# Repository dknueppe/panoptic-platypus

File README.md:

# Panoptic Platypus

This here is a new repository for an OSH/OSS data logger it will feature the
Lattice ecp5 for communication data processing. At this point there is no further
information.

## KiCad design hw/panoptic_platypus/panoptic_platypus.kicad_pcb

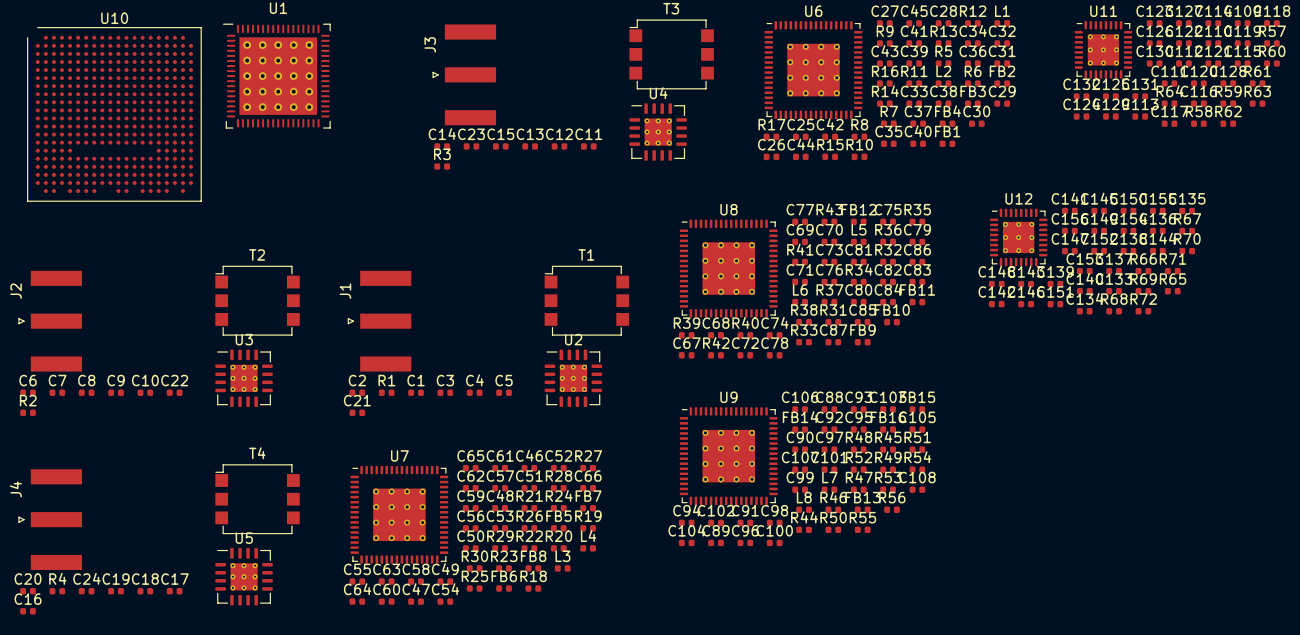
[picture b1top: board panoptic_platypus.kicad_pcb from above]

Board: 2 copper layers, 272 parts (0 on the bottom side), 218 nets, no tracks yet.

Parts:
C1, C6, C11, C16: 0.3p; C_0402_1005Metric
C2, C3, C7, C8, C12, C13, C17, C18, C25, C26, C27, C28, C31, C32, C33, C34, C38, C40, C41, C42, C43, C46, C47, C48, C49, C52, C53, C54, C55, C59, C61, C62, C63, C64, C67, C68, C69, C70, C73, C74, C75, C76, C80, C82, C83, C84, C85, C88, C89, C90, C91, C94, C95, C96, C97, C101, C103, C104, C105, C106, C115, C118, C122, C124, C127, C129, C131, C139, C142, C146, C148, C151, C153, C155: 0.1u; C_0402_1005Metric
C4, C9, C14, C19: 0.05p; C_0402_1005Metric
C5, C10, C15, C20, C29, C30, C35, C36, C50, C51, C56, C57, C71, C72, C77, C78, C92, C93, C98, C99: 10n; C_0402_1005Metric
C21, C22, C23, C24, C37, C39, C58, C60, C79, C81, C100, C102, C117, C119, C126, C141, C143, C150: 1u; C_0402_1005Metric
C44, C45, C65, C66, C86, C87, C107, C108: 5p; C_0402_1005Metric
C109, C110, C111, C112, C116, C121, C125, C128, C130, C132, C133, C134, C135, C136, C140, C145, C149, C152, C154, C156: 100p; C_0402_1005Metric
C113, C114, C137, C138: 0.01u; C_0402_1005Metric
C120, C144: 820p; C_0402_1005Metric
C123, C147: 0.012u; C_0402_1005Metric
FB1, FB5, FB9, FB13: 10 @ 100MHz; C_0402_1005Metric
FB2, FB3, FB4, FB6, FB7, FB8, FB10, FB11, FB12, FB14, FB15, FB16: 10 @ 100 MHz; C_0402_1005Metric
J1, J2, J3, J4: Conn_Coaxial; SMA_Amphenol_132289_EdgeMount
L1, L2, L3, L4, L5, L6, L7, L8: 100n; L_0402_1005Metric
R1, R2, R3, R4: 4.75k; R_0402_1005Metric
R5, R6, R7, R18, R19, R20, R31, R32, R33, R44, R45, R46: 10k; R_0402_1005Metric
R8, R10, R11, R13, R21, R23, R24, R26, R34, R36, R37, R39, R47, R49, R50, R52: 33; R_0402_1005Metric
R9, R12, R22, R25, R35, R38, R48, R51: 49.9; R_0402_1005Metric
R14, R15, R16, R17, R27, R28, R29, R30, R40, R41, R42, R43, R53, R54, R55, R56: 66; R_0402_1005Metric
R57, R58, R59, R60, R65, R66, R67, R68: 50; R_0402_1005Metric
R61, R69: 90.9; R_0402_1005Metric
R62, R70: 30.1; R_0402_1005Metric
R63, R71: 240; R_0402_1005Metric
R64, R72: 5.1k; R_0402_1005Metric
T1, T2, T3, T4: MABA-011082; Pulse_P0926NL
U1: MAX2851; TQFN-68_EP_10x10_Pitch0.5mm_EP7.7mmx7.7mm_ThermalVias
U2, U3, U4, U5: LTC5510; QFN-16-1EP_5x5mm_P0.8mm_EP2.7x2.7mm_ThermalVias
U6, U7, U8, U9: AD9268; LFCSP-64-1EP_9x9mm_P0.5mm_EP5.21x5.21mm_ThermalVias
U10: ECP5_5G_25_CABGA381; Lattice_caBGA-381_17.0x17.0mm_Layout20x20_P0.8mm_Ball0.4mm_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
U11, U12: MAX2871; TQFN-32-1EP_5x5mm_P0.5mm_EP3.1x3.1mm_ThermalVias

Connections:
+1V8: C25.1, C26.1, C27.1, C28.1, C29.1, C30.1, C31.1, C32.1, C33.1, C34.1, C35.1, C36.1, C46.1, C47.1, C48.1, C49.1, C50.1, C51.1, C52.1, C53.1, C54.1, C55.1, C56.1, C57.1, C67.1, C68.1, C69.1, C70.1, C71.1, C72.1, C73.1, C74.1, C75.1, C76.1, C77.1, C78.1, C88.1, C89.1, C90.1, C91.1, C92.1, C93.1, C94.1, C95.1, C96.1, C97.1, C98.1, C99.1, R6.1, R7.1, R19.1, R20.1, R32.1, R33.1, R45.1, R46.1, U6.10, U6.19, U6.28, U6.37, U6.49, U6.50, U6.53, U6.54, U6.59, U6.60, U6.63, U6.64, U7.10, U7.19, U7.28, U7.37, U7.49, U7.50, U7.53, U7.54, U7.59, U7.60, U7.63, U7.64, U8.10, U8.19, U8.28, U8.37, U8.49, U8.50, U8.53, U8.54, U8.59, U8.60, U8.63, U8.64, U9.10, U9.19, U9.28, U9.37, U9.49, U9.50, U9.53, U9.54, U9.59, U9.60, U9.63, U9.64
+5V: C5.1, C10.1, C15.1, C20.1, C21.1, C22.1, C23.1, C24.1, U2.6, U2.7, U3.6, U3.7, U4.6, U4.7, U5.6, U5.7
/ADC Path2/CSB: R7.2, U6.46
/ADC Path2/OEB: R6.2, U6.47
/ADC Path 1/CSB: R33.2, U8.46
/ADC Path 1/OEB: R32.2, U8.47
/ADC Path 3/CSB: R20.2, U7.46
/ADC Path 3/OEB: R19.2, U7.47
/ADC Path 4/CSB: R46.2, U9.46
/ADC Path 4/OEB: R45.2, U9.47
/I_OUT_A0: U8.25, U10.B20
/I_OUT_A1: U8.26, U10.B19
/I_OUT_A2: U8.27, U10.A19
/I_OUT_A3: U8.29, U10.A18
/I_OUT_A4: U8.30, U10.B18
/I_OUT_A5: U8.31, U10.C17
/I_OUT_A6: U8.32, U10.A17
/I_OUT_A7: U8.33, U10.B17
/I_OUT_A8: U8.34, U10.D16
/I_OUT_A9: U8.35, U10.B16
/I_OUT_A10: U8.36, U10.C16
/I_OUT_A11: U8.38, U10.A16
/I_OUT_A12: U8.39, U10.E15
/I_OUT_A13: U8.40, U10.C15
/I_OUT_A14: U8.41, U10.D15
/I_OUT_A15: U8.42, U10.B15
/I_OUT_B0: U6.25, U10.T17
/I_OUT_B1: U6.26, U10.U16
/I_OUT_B2: U6.27, U10.U17
/I_OUT_B3: U6.29, U10.U18
/I_OUT_B4: U6.30, U10.T18
/I_OUT_B5: U6.31, U10.R18
/I_OUT_B6: U6.32, U10.U19
/I_OUT_B7: U6.33, U10.T19
/I_OUT_B8: U6.34, U10.U20
/I_OUT_B9: U6.35, U10.R20
/I_OUT_B10: U6.36, U10.T20
/I_OUT_B11: U6.38, U10.P20
/I_OUT_B12: U6.39, U10.P18
/I_OUT_B13: U6.40, U10.N20
/I_OUT_B14: U6.41, U10.P19
/I_OUT_B15: U6.42, U10.N19
/I_OUT_C0: U7.25, U10.G2
/I_OUT_C1: U7.26, U10.H2
/I_OUT_C2: U7.27, U10.F1
/I_OUT_C3: U7.29, U10.G1
/I_OUT_C4: U7.30, U10.J4
/I_OUT_C5: U7.31, U10.J3
/I_OUT_C6: U7.32, U10.J5
/I_OUT_C7: U7.33, U10.K3
/I_OUT_C8: U7.34, U10.K2
/I_OUT_C9: U7.35, U10.H1
/I_OUT_C10: U7.36, U10.J1
/I_OUT_C11: U7.38, U10.K1
/I_OUT_C12: U7.39, U10.K4
/I_OUT_C13: U7.40, U10.L4
/I_OUT_C14: U7.41, U10.K5
/I_OUT_C15: U7.42, U10.L5
/I_OUT_D0: U9.25, U10.K20
/I_OUT_D1: U9.26, U10.K19
/I_OUT_D2: U9.27, U10.J20
/I_OUT_D3: U9.29, U10.J19
/I_OUT_D4: U9.30, U10.K18
/I_OUT_D5: U9.31, U10.H20
/I_OUT_D6: U9.32, U10.J18
/I_OUT_D7: U9.33, U10.G19
/I_OUT_D8: U9.34, U10.G20
/I_OUT_D9: U9.35, U10.F19
/I_OUT_D10: U9.36, U10.F20
/I_OUT_D11: U9.38, U10.E20
/I_OUT_D12: U9.39, U10.E19
/I_OUT_D13: U9.40, U10.D19
/I_OUT_D14: U9.41, U10.D20
/I_OUT_D15: U9.42, U10.C20
/LO_A+: C110.2, U2.15
/LO_A-: C109.2, U2.14
/LO_B+: C112.2, U3.15
/LO_B-: C111.2, U3.14
/LO_C+: C134.2, U4.15
/LO_C-: C133.2, U4.14
/LO_D+: C136.2, U5.15
/LO_D-: C135.2, U5.14
/LO_Generator 1/AVCC: C124.1, C125.1, C127.1, C128.1, C129.1, C130.1, C131.1, C132.1, C148.1, C149.1, C151.1, C152.1, C153.1, C154.1, C155.1, C156.1, U11.6, U11.10, U11.16, U11.17, U12.6, U12.10, U12.16, U12.17
/LO_Generator 1/DVCC: C115.1, C116.1, C118.1, C121.1, C139.1, C140.1, C142.1, C145.1, U11.28, U11.32, U12.28, U12.32
/LO_Generator 1/REF_CLK_IN: U1.50, U11.29
/LO_Generator 2/REF_CLK_IN: U1.51, U12.29
/Q_OUT_D0: U9.4, U10.J16
/Q_OUT_D1: U9.5, U10.H17
/Q_OUT_D2: U9.6, U10.J17
/Q_OUT_D3: U9.7, U10.H18
/Q_OUT_D4: U9.8, U10.H16
/Q_OUT_D5: U9.9, U10.G18
/Q_OUT_D6: U9.11, U10.G16
/Q_OUT_D7: U9.12, U10.F17
/Q_OUT_D8: U9.13, U10.F18
/Q_OUT_D9: U9.14, U10.E17
/Q_OUT_D10: U9.15, U10.E18
/Q_OUT_D11: U9.16, U10.D18
/Q_OUT_D12: U9.17, U10.F16
/Q_OUT_D13: U9.18, U10.E16
/Q_OUT_D14: U9.20, U10.D17
/Q_OUT_D15: U9.21, U10.C18
GND: C5.2, C10.2, C15.2, C20.2, C21.2, C22.2, C23.2, C24.2, C25.2, C26.2, C27.2, C28.2, C29.2, C30.2, C31.2, C32.2, C33.2, C34.2, C35.2, C36.2, C37.2, C38.2, C39.2, C46.2, C47.2, C48.2, C49.2, C50.2, C51.2, C52.2, C53.2, C54.2, C55.2, C56.2, C57.2, C58.2, C59.2, C60.2, C67.2, C68.2, C69.2, C70.2, C71.2, C72.2, C73.2, C74.2, C75.2, C76.2, C77.2, C78.2, C79.2, C80.2, C81.2, C88.2, C89.2, C90.2, C91.2, C92.2, C93.2, C94.2, C95.2, C96.2, C97.2, C98.2, C99.2, C100.2, C101.2, C102.2, C113.2, C114.2, C117.2, C119.2, C120.1, C123.2, C126.2, C137.2, C138.2, C141.2, C143.2, C144.1, C147.2, C150.2, J1.2, J2.2, J3.2, J4.2, R1.1, R2.1, R3.1, R4.1, R5.2, R18.2, R31.2, R44.2, R61.1, R64.1, R69.1, R72.1, T1.2, T2.2, T3.2, T4.2, U1.1, U1.22, U1.44, U1.45, U1.69, U2.4, U2.9, U2.12, U2.13, U2.16, U2.17, U3.4, U3.9, U3.12, U3.13, U3.16, U3.17, U4.4, U4.9, U4.12, U4.13, U4.16, U4.17, U5.4, U5.9, U5.12, U5.13, U5.16, U5.17, U6.56, U6.65, U7.56, U7.65, U8.56, U8.65, U9.56, U9.65, U10.B7, U10.B14, U10.C19, U10.D4, U10.F7, U10.F8, U10.F13, U10.F14, U10.G4, U10.G6, U10.G7, U10.G8, U10.G9, U10.G10, U10.G11, U10.G12, U10.G13, U10.G14, U10.G15, U10.G17, U10.H19, U10.J2, U10.J7, U10.J9, U10.J10, U10.J11, U10.J12, U10.J14, U10.K6, U10.K7, U10.K9, U10.K10, U10.K11, U10.K12, U10.K14, U10.K15, U10.L9, U10.L10, U10.L11, U10.L12, U10.M2, U10.M7, U10.M9, U10.M10, U10.M11, U10.M12, U10.M14, U10.M16, U10.N6, U10.N7, U10.N14, U10.N15, U10.P7, U10.P8, U10.P11, U10.P12, U10.P13, U10.P14, U10.R19, U10.U7, U10.U8, U10.U9, U10.U10, U10.U11, U10.U12, U10.U13, U10.U14, U10.V5, U10.V6, U10.V7, U10.V8, U10.V9, U10.V12, U10.V13, U10.V14, U10.V15, U10.V16, U10.V19, U10.V20, U10.W6, U10.W7, U10.W12, U10.W15, U10.W16, U10.W19, U11.8, U11.11, U11.18, U11.21, U11.27, U11.31, U11.33, U12.8, U12.11, U12.18, U12.21, U12.27, U12.31, U12.33
unnamed: C1.1, C2.1, T1.6
unnamed: C1.2, C3.1, T1.5
unnamed: C2.2, C4.1, U2.3
unnamed: C3.2, C4.2, U2.2
unnamed: C6.1, C7.1, T2.6
unnamed: C6.2, C8.1, T2.5
unnamed: C7.2, C9.1, U3.3
unnamed: C8.2, C9.2, U3.2
unnamed: C11.1, C12.1, T3.6
unnamed: C11.2, C13.1, T3.5
unnamed: C12.2, C14.1, U4.3
unnamed: C13.2, C14.2, U4.2
unnamed: C16.1, C17.1, T4.6
unnamed: C16.2, C18.1, T4.5
unnamed: C17.2, C19.1, U5.3
unnamed: C18.2, C19.2, U5.2
unnamed: C37.1, C38.1, U6.55
unnamed: C39.1, R8.1, R10.2, R11.1, R13.2, U6.57
unnamed: C40.1, FB1.2, R8.2, R9.1
unnamed: C41.1, FB2.2, R9.2, R10.1
unnamed: C42.1, FB3.2, R11.2, R12.1
unnamed: C43.1, FB4.2, R12.2, R13.1
unnamed: C44.1, FB2.1, R15.1
unnamed: C44.2, FB1.1, R14.1
unnamed: C45.1, FB4.1, R17.1
unnamed: C45.2, FB3.1, R16.1
unnamed: C58.1, C59.1, U7.55
unnamed: C60.1, R21.1, R23.2, R24.1, R26.2, U7.57
unnamed: C61.1, FB5.2, R21.2, R22.1
unnamed: C62.1, FB6.2, R22.2, R23.1
unnamed: C63.1, FB7.2, R24.2, R25.1
unnamed: C64.1, FB8.2, R25.2, R26.1
unnamed: C65.1, FB6.1, R28.1
unnamed: C65.2, FB5.1, R27.1
unnamed: C66.1, FB8.1, R30.1
unnamed: C66.2, FB7.1, R29.1
unnamed: C79.1, C80.1, U8.55
unnamed: C81.1, R34.1, R36.2, R37.1, R39.2, U8.57
unnamed: C82.1, FB9.2, R34.2, R35.1
unnamed: C83.1, FB10.2, R35.2, R36.1
unnamed: C84.1, FB11.2, R37.2, R38.1
unnamed: C85.1, FB12.2, R38.2, R39.1
unnamed: C86.1, FB10.1, R41.1
unnamed: C86.2, FB9.1, R40.1
unnamed: C87.1, FB12.1, R43.1
unnamed: C87.2, FB11.1, R42.1
unnamed: C100.1, C101.1, U9.55
unnamed: C102.1, R47.1, R49.2, R50.1, R52.2, U9.57
unnamed: C103.1, FB13.2, R47.2, R48.1
unnamed: C104.1, FB14.2, R48.2, R49.1
unnamed: C105.1, FB15.2, R50.2, R51.1
unnamed: C106.1, FB16.2, R51.2, R52.1
unnamed: C107.1, FB14.1, R54.1
unnamed: C107.2, FB13.1, R53.1
unnamed: C108.1, FB16.1, R56.1
unnamed: C108.2, FB15.1, R55.1
unnamed: C109.1, R57.1, U11.13
unnamed: C110.1, R58.1, U11.12
unnamed: C111.1, R59.1, U11.15
unnamed: C112.1, R60.1, U11.14
unnamed: C113.1, C114.1, R57.2, R58.2, R59.2, R60.2
unnamed: C115.2, C116.2, C118.2, C121.2
unnamed: C117.1, U11.19
unnamed: C119.1, U11.23
unnamed: C120.2, R63.2, U11.20
unnamed: C122.1, C123.1, R63.1, U11.7
unnamed: C122.2, R62.2
unnamed: C124.2, C125.2, C127.2, C128.2, C129.2, C130.2, C131.2, C132.2
unnamed: C126.1, U11.24
unnamed: C133.1, R65.1, U12.13
unnamed: C134.1, R66.1, U12.12
unnamed: C135.1, R67.1, U12.15
unnamed: C136.1, R68.1, U12.14
unnamed: C137.1, C138.1, R65.2, R66.2, R67.2, R68.2
unnamed: C139.2, C140.2, C142.2, C145.2
unnamed: C141.1, U12.19
unnamed: C143.1, U12.23
unnamed: C144.2, R71.2, U12.20
unnamed: C146.1, C147.1, R71.1, U12.7
unnamed: C146.2, R70.2
unnamed: C148.2, C149.2, C151.2, C152.2, C153.2, C154.2, C155.2, C156.2
unnamed: C150.1, U12.24
unnamed: J1.1, T1.1
unnamed: J2.1, T2.1
unnamed: J3.1, T3.1
unnamed: J4.1, T4.1
unnamed: L1.1, R14.2, U6.51
unnamed: L1.2, R15.2, U6.52
unnamed: L2.1, R16.2, U6.62
unnamed: L2.2, R17.2, U6.61
unnamed: L3.1, R27.2, U7.51
unnamed: L3.2, R28.2, U7.52
unnamed: L4.1, R29.2, U7.62
unnamed: L4.2, R30.2, U7.61
unnamed: L5.1, R40.2, U8.51
unnamed: L5.2, R41.2, U8.52
unnamed: L6.1, R42.2, U8.62
unnamed: L6.2, R43.2, U8.61
unnamed: L7.1, R53.2, U9.51
unnamed: L7.2, R54.2, U9.52
unnamed: L8.1, R55.2, U9.62
unnamed: L8.2, R56.2, U9.61
unnamed: R1.2, U2.8
unnamed: R2.2, U3.8
unnamed: R3.2, U4.8
unnamed: R4.2, U5.8
unnamed: R5.1, U6.58
unnamed: R18.1, U7.58
unnamed: R31.1, U8.58
unnamed: R44.1, U9.58
unnamed: R61.2, R62.1, U11.5
unnamed: R64.2, U11.22
unnamed: R69.2, R70.1, U12.5
unnamed: R72.2, U12.22
VCC: U10.F6, U10.F15, U10.H8, U10.H9, U10.H10, U10.H11, U10.H12, U10.H13, U10.J8, U10.J13, U10.K8, U10.K13, U10.L8, U10.L13, U10.M8, U10.M13, U10.N8, U10.N9, U10.N10, U10.N11, U10.N12, U10.N13, U10.P6, U10.P15, U10.T6, U10.T7, U10.T8, U10.T9, U10.T10, U10.U6, U10.V10, U10.V11

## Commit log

2020-09-12 added gitignore
2020-09-12 updated gitignore and started on schematic
2020-09-20 changed input stage to be hierachial
2020-09-26 Added ADC decoupling and input filter
2020-09-27 adc stage shematic finished
2020-10-03 updated some symbols added some ICs
2020-10-05 Added LO Generator, fixed some smybols
2020-10-12 added power supply, connected up some bits
2020-10-19 updated power scheme
